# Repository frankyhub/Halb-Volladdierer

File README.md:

<div align="center">

|[:skull:ISSUE](https://github.com/frankyhub/Halb-Volladdierer/issues?q=is%3Aissue)|[:speech_balloon: Forum /Discussion](https://github.com/frankyhub/Halb-Volladdierer/discussions)|[:grey_question:WiKi](https://github.com/frankyhub/Halb-Volladdierer/wiki)||
|--|--|--|--|
| | | | |
<a href="https://github.com/frankyhub/Halb-Volladdierer/issues">|<a href="https://github.com/frankyhub/Halb-Volladdierer/discussions">|<a href="https://github.com/frankyhub/Halb-Volladdierer/6eleases">||
|| <a href="https://github.com/frankyhub/Halb-Volladdierer/pulse" alt="Activity">| <a href="https://github.com/frankyhub/Halb-Volladdierer/graphs/traffic">  |<a href="https://github.com/frankyhub?tab=stars"> ||

# Halb-Volladdierer

<br> <br>
 
<br> <br>
 
<br> <br>

## 2 Halbaddierer -> Volladdierer

<br> <br>

## 4Bit Addierer/Subtrahierer

<br> <br>

## 74LS83 4Bit 4Bit Addierer/Subtrahierer

<br> <br>

---

<div style="position:absolute; left:2cm; ">   
<ol class="breadcrumb" style="border-top: 2px solid black;border-bottom:2px solid black; height: 45px; width: 900px;"> <p align="center"><a href="#oben">nach oben</a></p></ol>
</div>  

---

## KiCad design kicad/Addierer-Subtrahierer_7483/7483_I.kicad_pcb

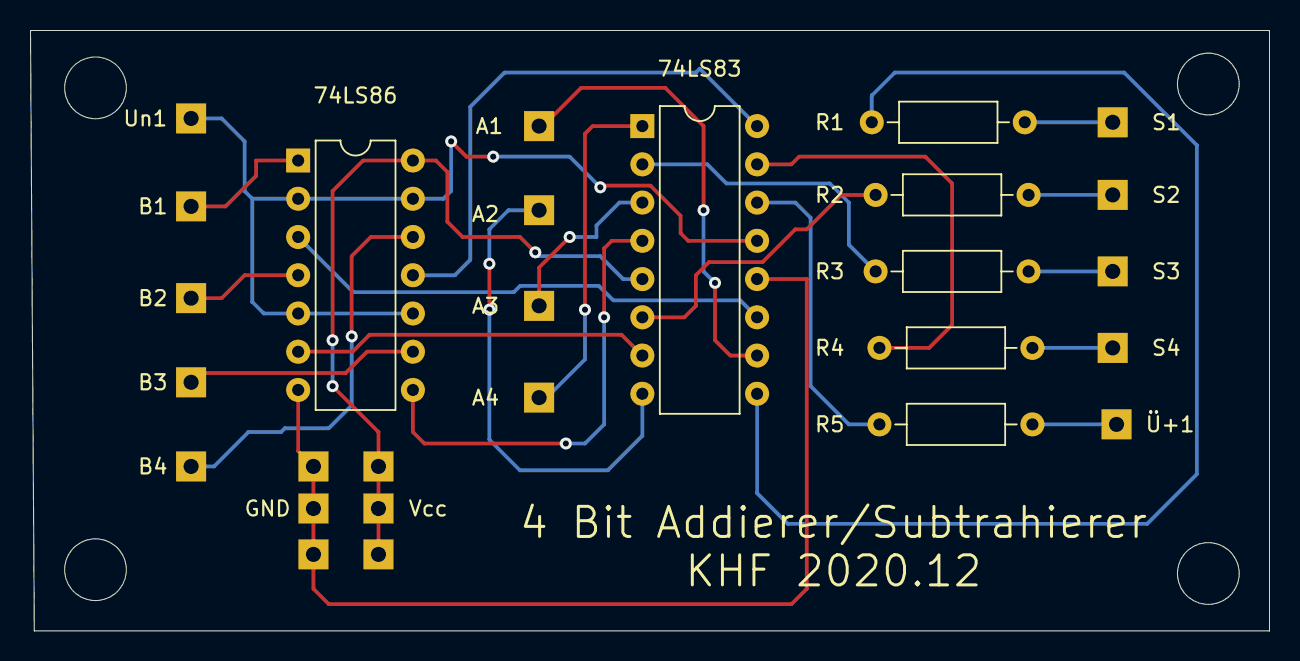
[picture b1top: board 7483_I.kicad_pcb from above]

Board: 2 copper layers, 82.3 x 39.9 mm, 27 parts (0 on the bottom side), 25 nets.

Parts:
74LS83: 7483; DIP-16_W7.62mm
74LS86: 7486; DIP-14_W7.62mm
A1: A1; LP
A2: A2; LP
A3: A3; LP
A4: A4; LP
B1: B1; LP
B2: B2; LP
B3: B3; LP
B4: B4; LP
GND: LP_E; LP
GND#2, GND#3: LP_A; LP
R1, R2, R3, R4, R5: R; R_Axial_DIN0207_L6.3mm_D2.5mm_P10.16mm_Horizontal
S1, S2, S3, S4: LP_E; LP
Un1: Un1; LP
Vcc: LP_A; LP
Vcc#2, Vcc#3: LP_A; LP
Ü+1: LP_E; LP

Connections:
+5V: 74LS83.5, 74LS86.14, Vcc.1, Vcc#2.1, Vcc#3.1
GND: 74LS83.12, 74LS86.7, GND.1, GND#2.1, GND#3.1
unnamed: R1.1, S1.1
unnamed: 74LS83.9, R1.2
unnamed: R2.1, S2.1
unnamed: 74LS83.6, R2.2
unnamed: R3.1, S3.1
unnamed: 74LS83.2, R3.2
unnamed: R4.1, S4.1
unnamed: 74LS83.15, R4.2
unnamed: R5.1, Ü+1.1
unnamed: 74LS83.14, R5.2
unnamed: 74LS83.13, 74LS86.2, 74LS86.5, 74LS86.10, 74LS86.13, Un1.1
unnamed: 74LS86.1, B1.1
unnamed: 74LS86.4, B2.1
unnamed: 74LS86.9, B3.1
unnamed: 74LS86.12, B4.1
unnamed: 74LS83.8, A2.1
unnamed: 74LS83.3, A3.1
unnamed: 74LS83.1, A4.1
unnamed: 74LS83.4, 74LS86.8
unnamed: 74LS83.7, 74LS86.6
unnamed: 74LS83.10, A1.1
unnamed: 74LS83.11, 74LS86.3
unnamed: 74LS83.16, 74LS86.11

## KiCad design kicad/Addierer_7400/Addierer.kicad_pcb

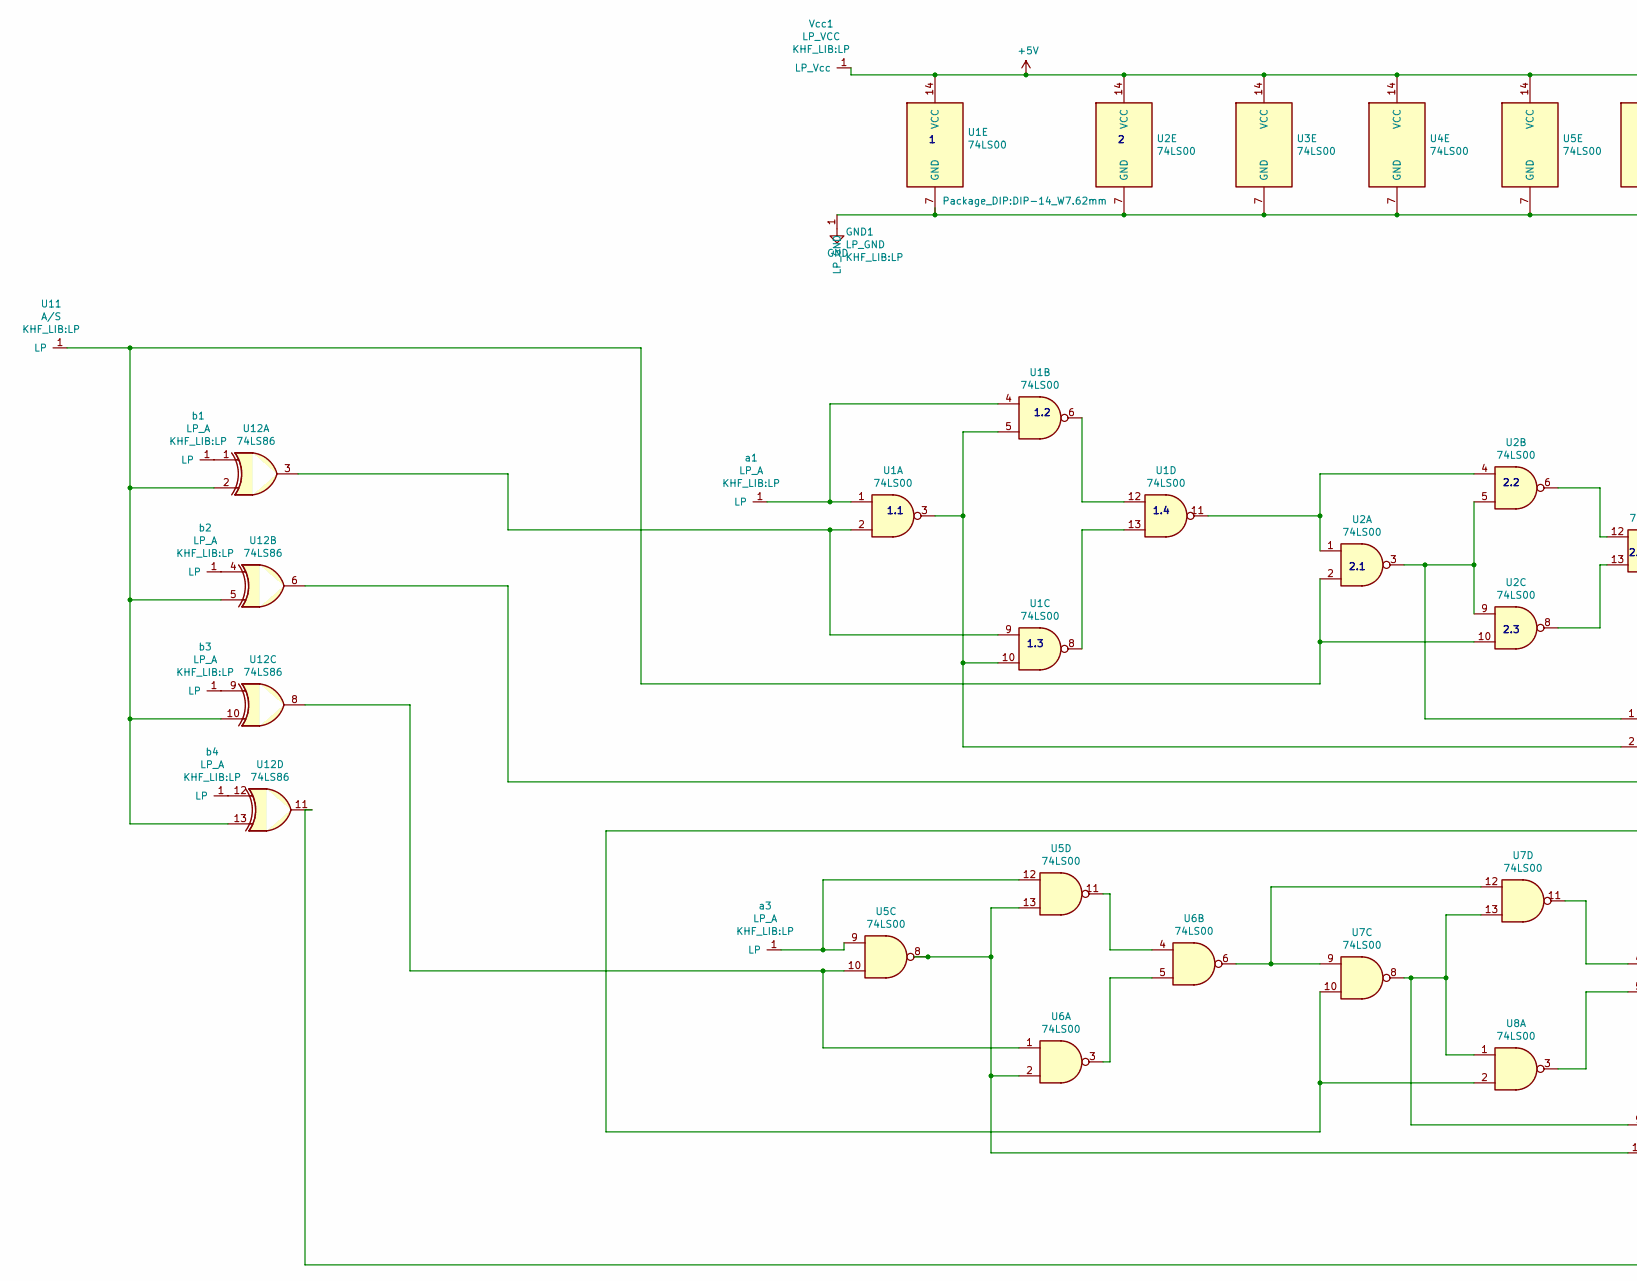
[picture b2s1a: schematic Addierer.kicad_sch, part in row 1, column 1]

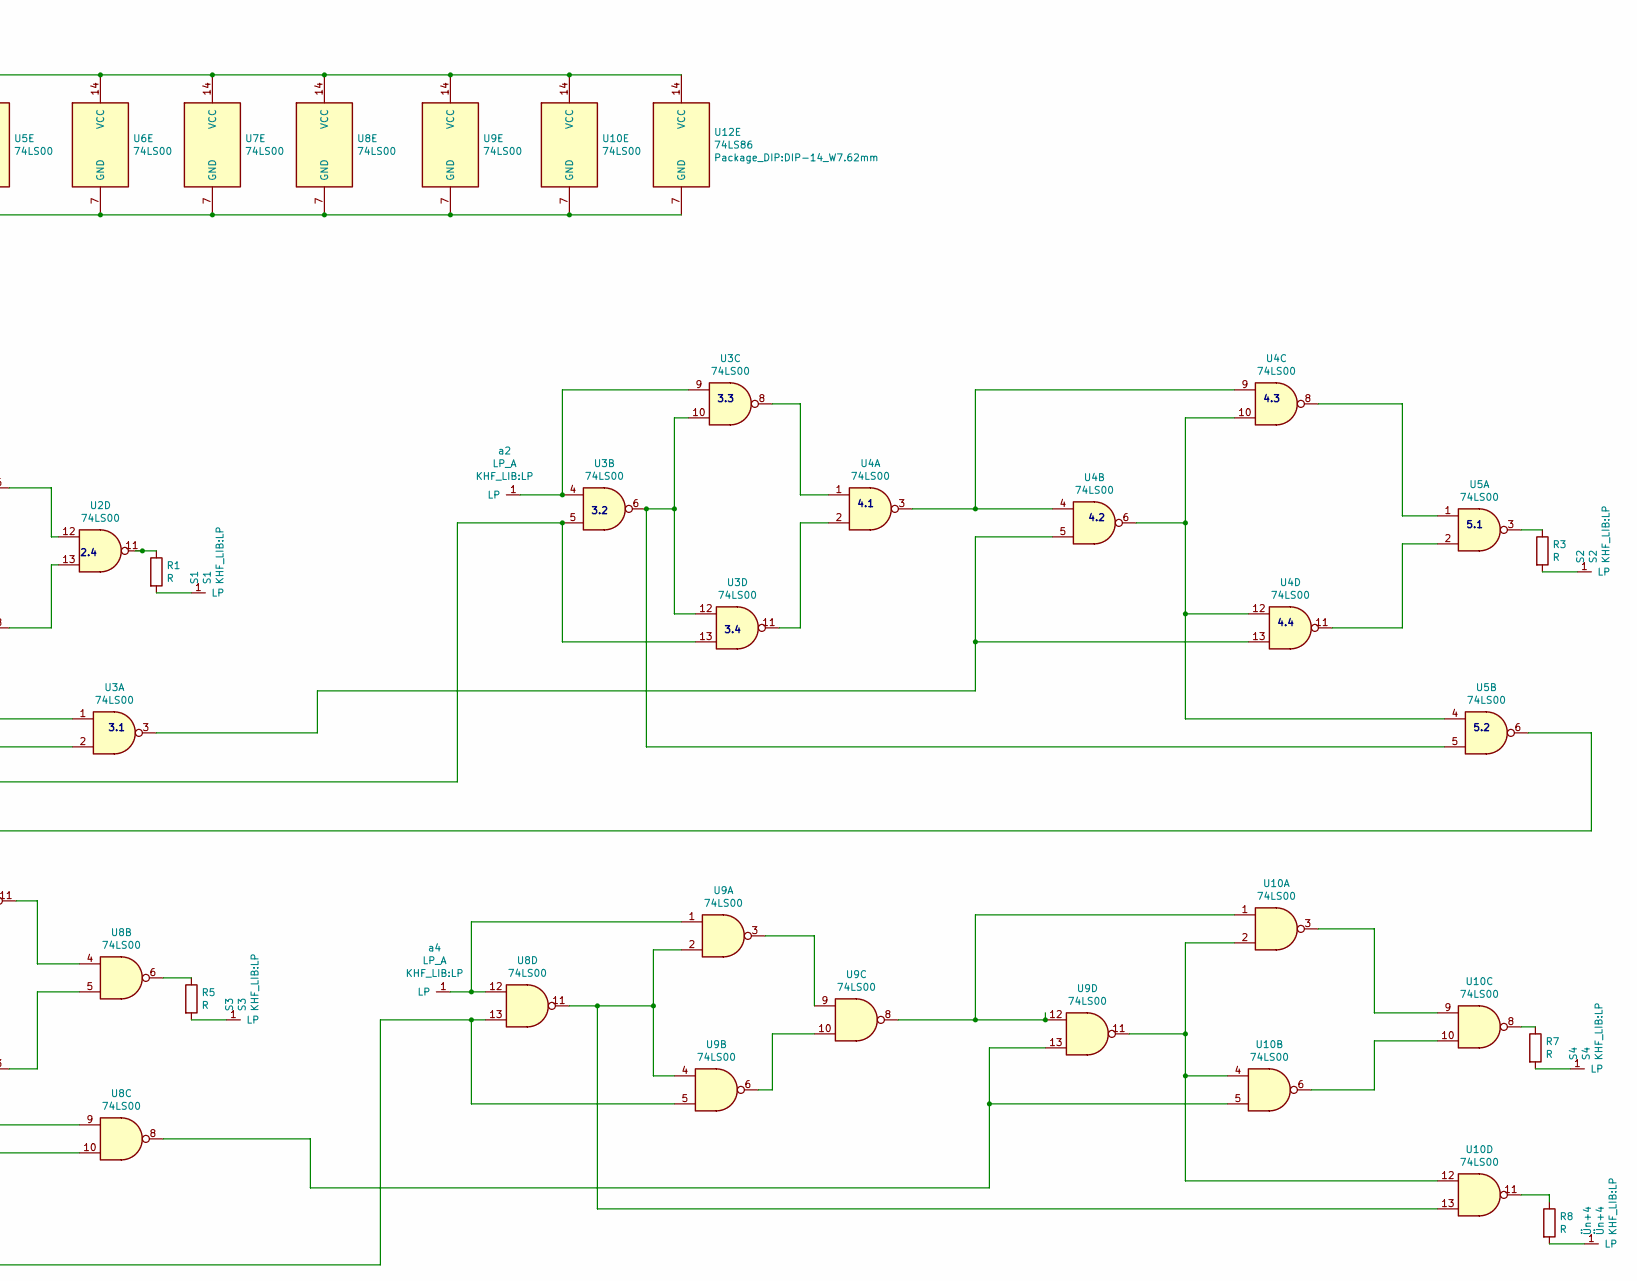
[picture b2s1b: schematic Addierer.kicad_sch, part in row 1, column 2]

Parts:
GND1: LP_GND; LP
R1, R3, R5, R7, R8: R; R_Axial_DIN0207_L6.3mm_D2.5mm_P7.62mm_Horizontal
S1: S1; LP
S2: S2; LP
S3: S3; LP
S4: S4; LP
U1, U2, U3, U4, U5, U6, U7, U8, U9, U10: 74LS00; DIP-14_W7.62mm
U11: A/S; LP
U12: 74LS86; DIP-14_W7.62mm
Vcc1: LP_VCC; LP
a1, a2, a3, a4: LP_A; LP
b1, b2, b3, b4: LP_A; LP
Ün+4: Ün+4; LP

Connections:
+5V: U1.14 (VCC), U2.14 (VCC), U3.14 (VCC), U4.14 (VCC), U5.14 (VCC), U6.14 (VCC), U7.14 (VCC), U8.14 (VCC), U9.14 (VCC), U10.14 (VCC), U12.14 (VCC), Vcc1.1; also elsewhere on the board
unnamed 1: GND1.1, U1.7 (GND), U2.7 (GND), U3.7 (GND), U4.7 (GND), U5.7 (GND), U6.7 (GND), U7.7 (GND), U8.7 (GND), U9.7 (GND), U10.7 (GND), U12.7 (GND); also elsewhere on the board
unnamed: R1.1, U2.11
unnamed: R1.2, S1.1
unnamed: R3.1, U5.3
unnamed: R3.2, S2.1
unnamed: R5.1, U8.6
unnamed: R5.2, S3.1
unnamed: R7.1, U10.8
unnamed: R7.2, S4.1
unnamed: R8.1, U10.11
unnamed: R8.2, Ün+4.1
unnamed: U1.1, U1.4, a1.1
unnamed: U1.2, U1.9, U12.3
unnamed: U1.3, U1.5, U1.10, U3.2
unnamed: U1.11, U2.1, U2.4
unnamed: U1.6, U1.12
unnamed: U1.8, U1.13
unnamed: U2.3, U2.5, U2.9, U3.1
unnamed: U2.6, U2.12
unnamed: U2.8, U2.13
unnamed: U3.3, U4.5, U4.13
unnamed: U3.4, U3.9, a2.1
unnamed: U3.8, U4.1
unnamed: U3.6, U3.10, U3.12, U5.5
unnamed: U3.11, U4.2
unnamed: U4.3, U4.4, U4.9
unnamed: U4.8, U5.1
unnamed: U4.6, U4.10, U4.12, U5.4
unnamed: U4.11, U5.2
unnamed: U5.6, U7.10, U8.2
unnamed: U5.11, U6.4
unnamed: U5.9, U5.12, a3.1
unnamed: U5.8, U5.13, U6.2, U8.10
unnamed: U6.3, U6.5
unnamed: U6.6, U7.9, U7.12
unnamed: U7.11, U8.4
unnamed: U7.8, U7.13, U8.1, U8.9
unnamed: U8.3, U8.5
unnamed: U8.12, U9.1, a4.1
unnamed: U9.3, U9.9
unnamed: U9.6, U9.10
unnamed: U9.8, U9.12, U10.1
unnamed: U10.3, U10.9
unnamed: U8.8, U9.13, U10.5
unnamed: U10.6, U10.10
unnamed: U9.11, U10.2, U10.4, U10.12
unnamed: U8.11, U9.2, U9.4, U10.13
unnamed: U2.2, U2.10, U11.1, U12.2, U12.5, U12.10, U12.13
unnamed: U12.1, b1.1
unnamed: U12.4, b2.1
unnamed: U3.5, U3.13, U12.6
unnamed: U5.10, U6.1, U12.8
unnamed: U12.9, b3.1
unnamed: U8.13, U9.5, U12.11
unnamed: U12.12, b4.1

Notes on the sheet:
4.2
2.2
1.4
3.2
2.3
3.4
2.1
5.1
3.3
1.2
1.3
1.1
4.4
3.1
2.4
4.1
5.2
4.3

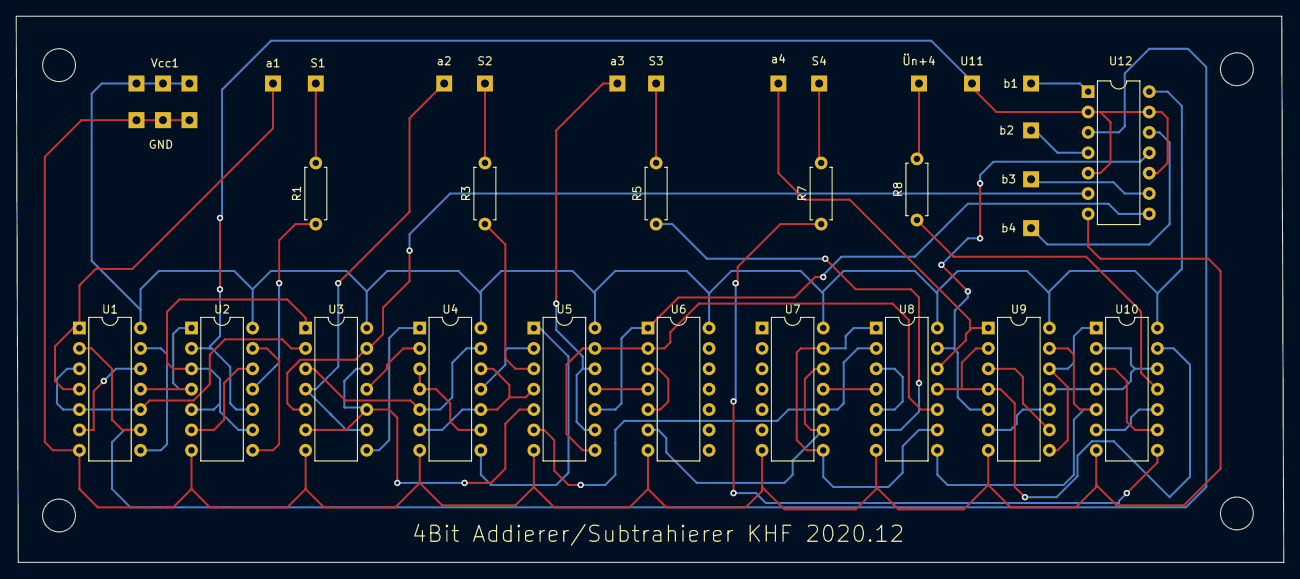
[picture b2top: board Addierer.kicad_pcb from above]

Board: 2 copper layers, 158.0 x 68.1 mm, 36 parts (0 on the bottom side), 56 nets.

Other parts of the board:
GND: LP_VCC; LP
Vcc1#2, Vcc1#3, Vcc1#4: LP_VCC; LP

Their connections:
+5V: Vcc1#3.1, Vcc1#4.1; also elsewhere on the board
unnamed 1: GND.1, Vcc1#2.1; also elsewhere on the board

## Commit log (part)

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2024-08-16 V 16.08.2024
2024-08-16 V 18.08.2024
2024-10-12 V12102024
